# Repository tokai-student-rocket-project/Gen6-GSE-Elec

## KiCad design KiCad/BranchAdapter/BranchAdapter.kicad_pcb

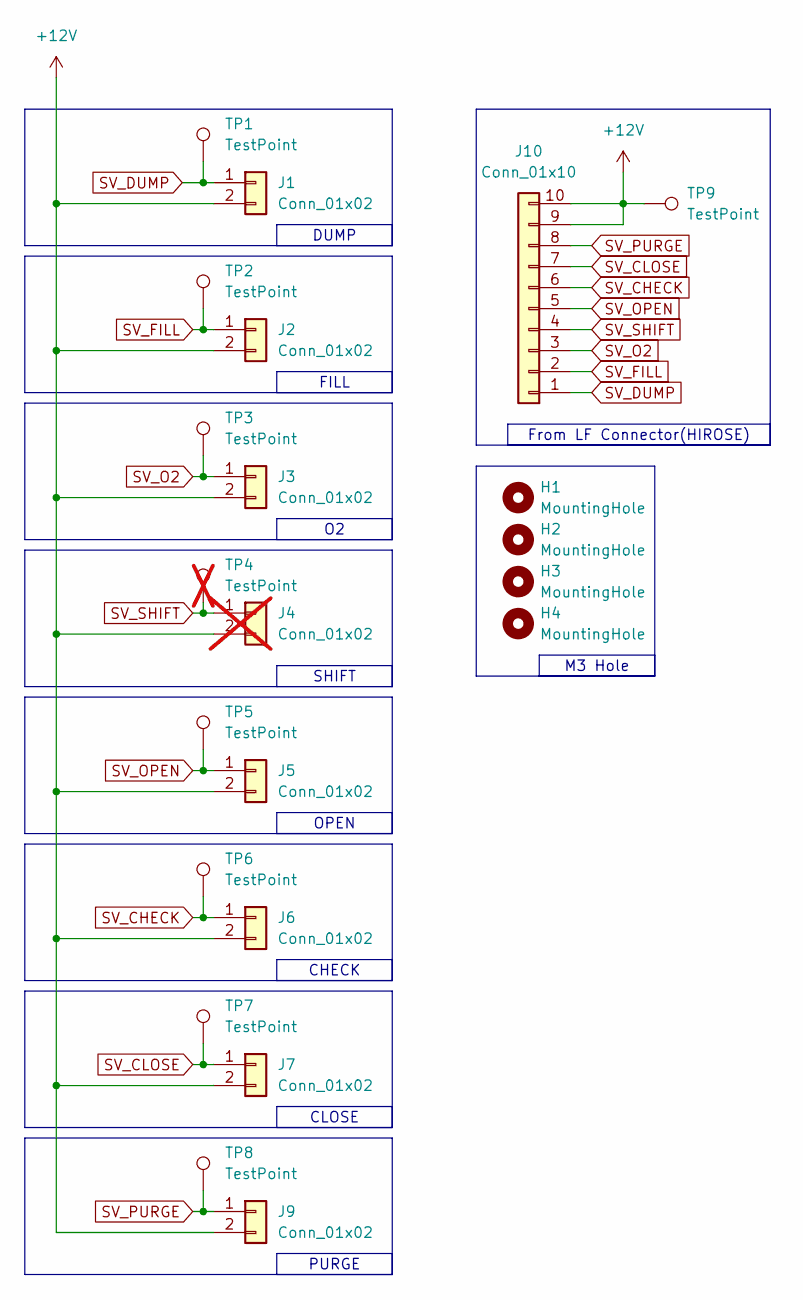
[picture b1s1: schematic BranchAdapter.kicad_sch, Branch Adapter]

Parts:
H1, H2, H3, H4: MountingHole; MountingHole_3.2mm_M3
J1, J2, J3, J5, J6, J7, J9: Conn_01x02; DF51A-2P-2DSA(01)
J4: Conn_01x02; DF51A-2P-2DSA(01); not fitted
J10: Conn_01x10; DF51A-10DP-2DS(20)
TP1, TP2, TP3, TP5, TP6, TP7, TP8, TP9: TestPoint; TestPoint_THTPad_D2.0mm_Drill1.0mm
TP4: TestPoint; TestPoint_THTPad_D2.0mm_Drill1.0mm; not fitted

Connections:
+12V: J1.2, J2.2, J3.2, J4.2, J5.2, J6.2, J7.2, J9.2, J10.9, J10.10, TP9.1
SV_CHECK: J6.1, J10.6, TP6.1
SV_CLOSE: J7.1, J10.7, TP7.1
SV_DUMP: J1.1, J10.1, TP1.1
SV_FILL: J2.1, J10.2, TP2.1
SV_O2: J3.1, J10.3, TP3.1
SV_OPEN: J5.1, J10.5, TP5.1
SV_PURGE: J9.1, J10.8, TP8.1
SV_SHIFT: J4.1, J10.4, TP4.1

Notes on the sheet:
CHECK
SHIFT
CLOSE
M3 Hole
From LF Connector(HIROSE)
FILL
OPEN
PURGE
DUMP

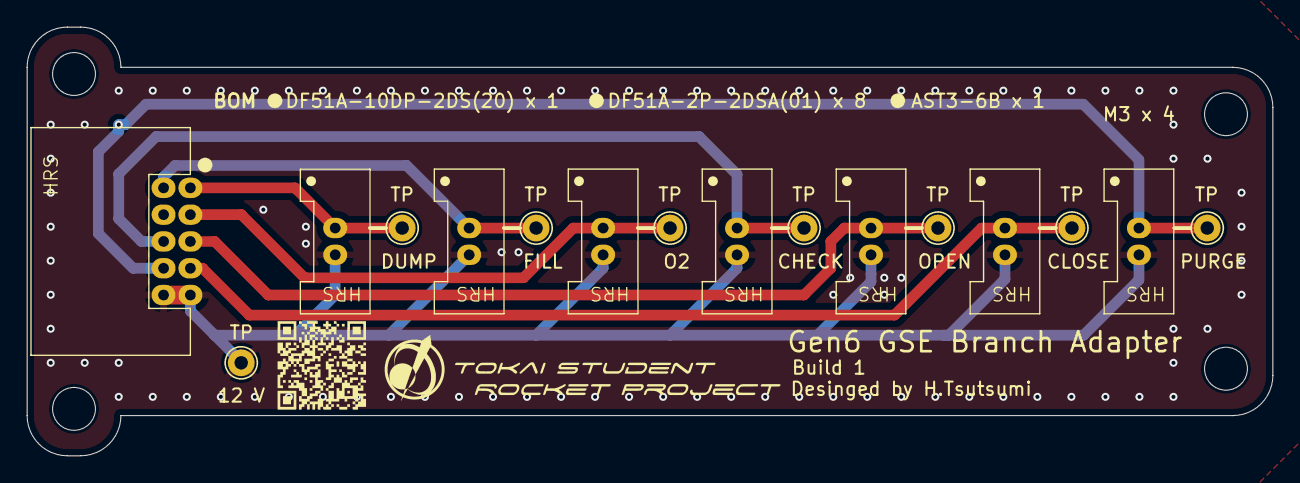
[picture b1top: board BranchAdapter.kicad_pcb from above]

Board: 2 copper layers, 93.0 x 32.0 mm, 20 parts (0 on the bottom side), 8 nets.
